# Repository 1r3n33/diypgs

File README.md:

# diypgs 🎮

The DIY portable game system.

# Electronics (schematics, PCB) 🪛🧰

Easy, cheap, and Arduino based...

### 👉 [**Making of the 1st board explained with pictures!**](./make/README.md) 📷

---

# Software (development kit & games) 🧑‍💻🤖

Develop your own games with provided SDK and example!

# 3D printing (case) 🚧👷

TBD

# Shop 🛒💸

If you are interested in getting one, please contact icaroulle+diypgs@gmail.com.

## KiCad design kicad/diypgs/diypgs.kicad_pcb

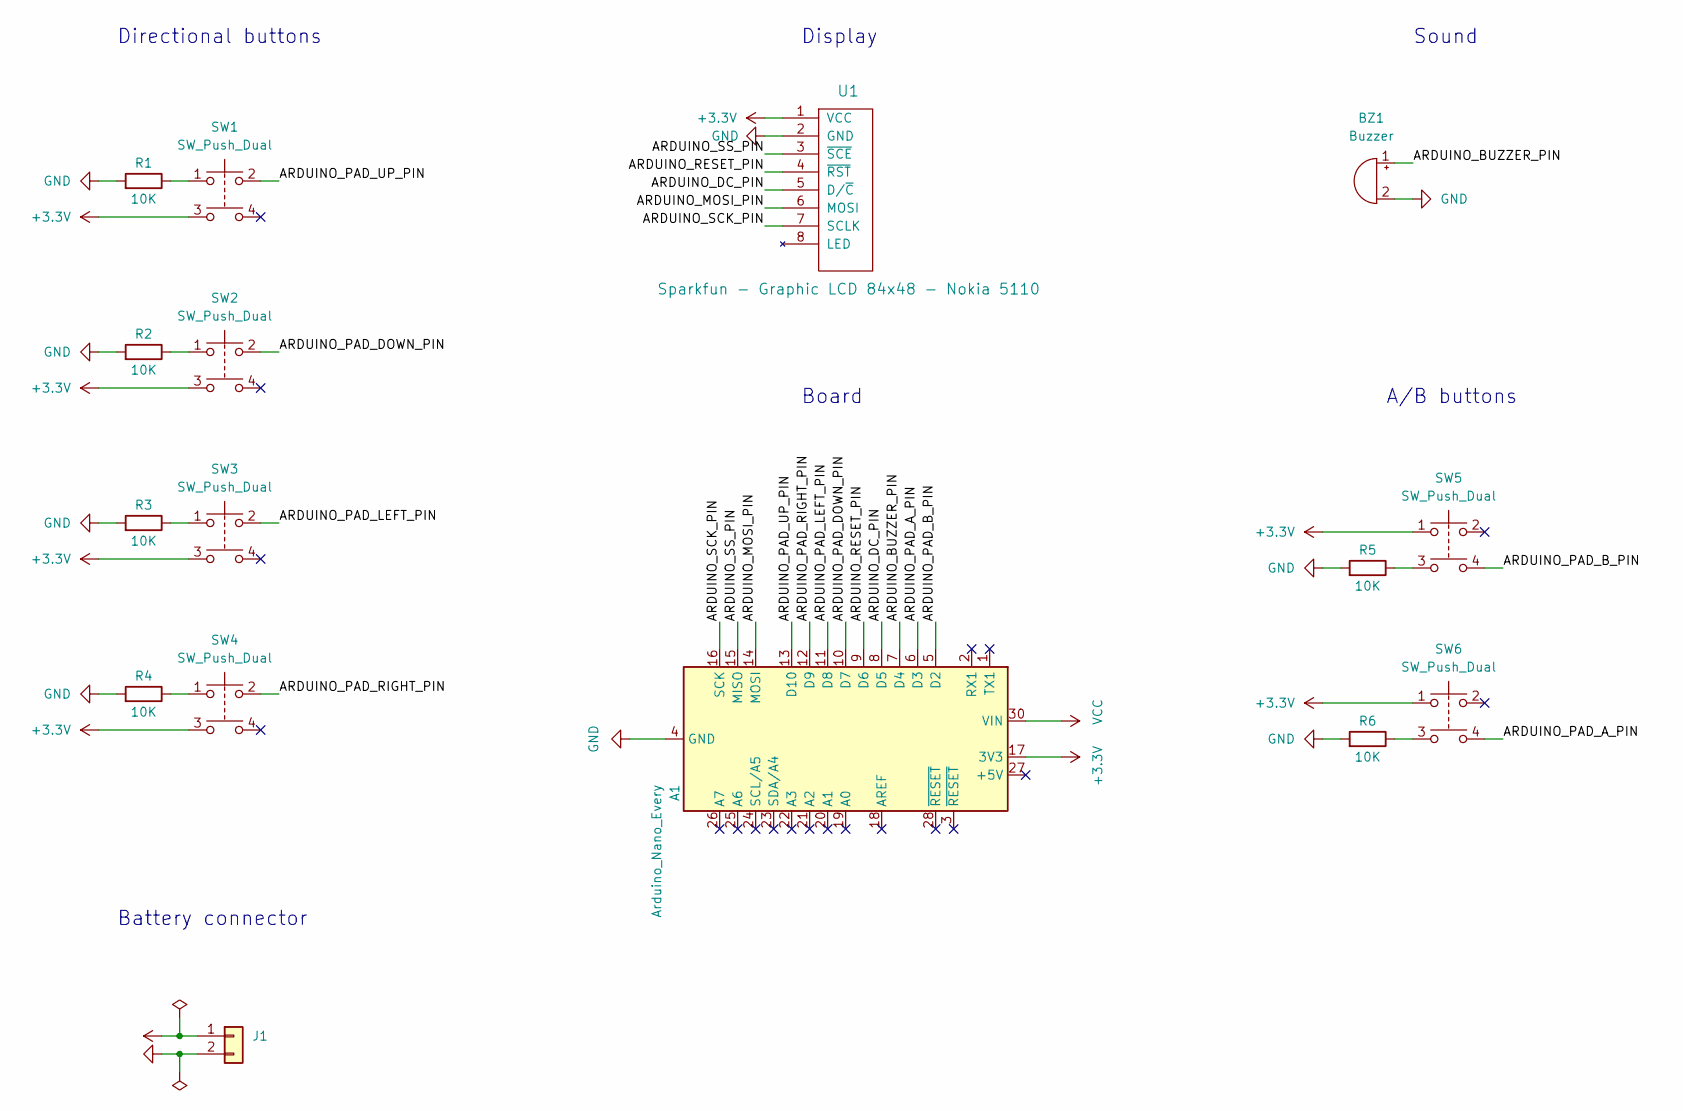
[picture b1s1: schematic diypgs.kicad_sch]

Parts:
A1: Arduino_Nano_Every; Arduino_Nano
BZ1: Buzzer; Buzzer_12x9.5RM7.6
J1: (no value)
R1, R2, R3, R4, R5, R6: 10K; R_Axial_DIN0207_L6.3mm_D2.5mm_P7.62mm_Horizontal
SW1, SW2, SW3, SW4, SW5, SW6: SW_Push_Dual; SW_PUSH_6mm_ALT
U1: Sparkfun - Graphic LCD 84x48 - Nokia 5110

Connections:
+3V3: A1.17 (3V3), SW1.3, SW2.3, SW3.3, SW4.3, SW5.1, SW6.1, U1.1 (VCC)
/ARDUINO_BUZZER_PIN: A1.7 (D4), BZ1.1 (-)
/ARDUINO_DC_PIN: A1.8 (D5), U1.5 (D/~C)
/ARDUINO_MOSI_PIN: A1.14 (MOSI), U1.6 (MOSI)
/ARDUINO_PAD_A_PIN: A1.6 (D3), SW6.4
/ARDUINO_PAD_B_PIN: A1.5 (D2), SW5.4
/ARDUINO_PAD_DOWN_PIN: A1.10 (D7), SW2.2
/ARDUINO_PAD_LEFT_PIN: A1.11 (D8), SW3.2
/ARDUINO_PAD_RIGHT_PIN: A1.12 (D9), SW4.2
/ARDUINO_PAD_UP_PIN: A1.13 (D10), SW1.2
/ARDUINO_RESET_PIN: A1.9 (D6), U1.4 (~RST)
/ARDUINO_SCK_PIN: A1.16 (SCK), U1.7 (SCLK)
/ARDUINO_SS_PIN: A1.15 (MISO), U1.3 (~SCE)
GND: A1.4 (GND), A1.29 (GND), BZ1.2 (+), R1.2, R2.2, R3.2, R4.2, R5.2, R6.2, U1.2 (GND)
unnamed: J1.1, J1.2
unnamed: R1.1, SW1.1
unnamed: R2.1, SW2.1
unnamed: R3.1, SW3.1
unnamed: R4.1, SW4.1
unnamed: R5.1, SW5.3
unnamed: R6.1, SW6.3
VCC: A1.30 (VIN)

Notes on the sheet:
Sound
Display
A/B buttons
Directional buttons
Battery connector
Board

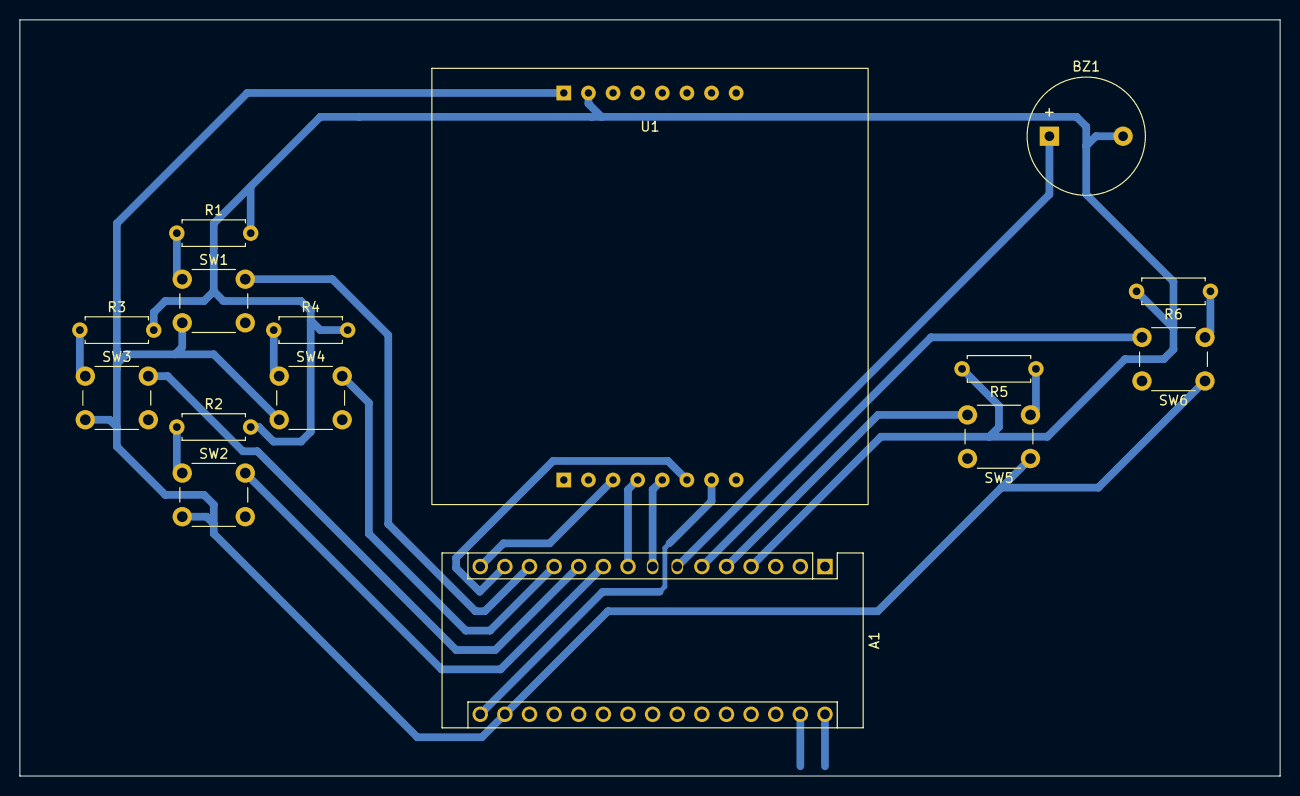
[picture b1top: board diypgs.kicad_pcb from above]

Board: 2 copper layers, 130.0 x 78.0 mm, 15 parts (0 on the bottom side), 20 nets.

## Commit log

2022-04-02 Blinking screen
2022-04-03 Draw sphere
2022-04-03 Use SPI
2022-04-05 Draw multiple sprites
2022-04-06 Add paddles
2022-04-07 Add clear and more gfx
2022-04-09 Fix clear loop
2022-04-09 Add framebuffer
2022-04-10 Optimization
2022-04-10 Introduce sprites
2022-04-11 Introduce PCD8544 lib
2022-04-12 Animate paddles
2022-04-13 Animate ball
2022-04-15 Ball collisions
2022-04-18 Paddles follow the ball
2022-04-19 Reorg files
2022-04-23 Ball collides with paddles
2022-04-26 Add controller input
2022-04-28 Clean ball position buffer
2022-04-29 Introduce controller
2022-05-01 Introduce SDK
2022-05-01 Fix loop to 30Hz
2022-05-02 Add sound
2022-05-04 Add XCLIP draw mode
2022-05-04 Player can score
2022-05-05 Add ball acceleration
2022-05-07 Add README
2022-05-08 Add GitHub actions
2022-05-09 Add KiCad project
2022-05-11 Introduce CollisionResult struct
2022-05-11 Fix bounce on paddle
2022-05-12 Introduce Bonus
2022-05-12 Clean C++ Bonus files
2022-05-13 Invert controls on bonus capture
2022-05-14 Add PCB design
2022-05-15 Add ball acceleration bonus
2022-05-15 Bonus fade in & out
2022-05-16 Add bonus motion
2022-05-16 Fix button pad number
2022-05-17 Add PCB tracks
2022-05-17 Fix ball bouncing back into the game
2022-05-20 Fix screen symbol and footprint
2022-05-20 Fix warnings
2022-05-20 Move arduino code to dedicated folder
2022-05-22 All tracks routed
2022-05-22 Clean Pcd8544 class
2022-05-22 Clean Gamepad class
2022-05-22 Clean Buzzer class
2022-05-23 Fix hw namespace
2022-05-24 Clean Collision class
2022-05-24 Introduce World
2022-05-25 Introduce world management logic
2022-05-26 Add logo
2022-05-27 Fix PCB design
2022-05-27 Use constexpr for graphics
2022-05-28 Add JST connector
2022-05-28 Add arduino:avr:nano build target
2022-05-29 Introduce Vector
2022-05-30 Use Vec2f16 for position
2022-06-01 Add multiple balls
2022-06-11 Support nano every
2022-06-11 Prepare bonus that changes paddle size
2022-06-11 Clean Paddle class
2022-06-11 Can change paddle size
2022-06-13 Paddle blinking before applying bonus effect
2022-06-14 Clean CircularBuffer class
2022-06-18 Recipe to make PCB
2022-06-23 Board modification after initial PCB prototype
2022-06-24 Thinner PCB tracks
2022-06-29 Move tracks to background layer
